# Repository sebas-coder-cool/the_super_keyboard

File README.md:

[keyboard (1).csv](https://github.com/user-attachments/files/33207110/keyboard.1.csv)
# The Super Keyboard

The Super Keyboard is an amazing keyboard that lets you attach a detachable screen. 
This screen can transform into a digital notebook — and the best part is that you
can also set up your Spotify on it.
## Features
- Clickable screen
- Digital notebook mode
- Detachable, dual-side screen mount

## Usage
Using the keyboard is simple: just connect it to your computer and start typing. 
Attach the screen to take notes directly on the digital notebook.

## License
- *cc by-nc-sa 4.0*
- full licence link: https://creativecommons.org/licenses/by-nc-sa/4.0/legalcode

## bom

[Bekijk de BOM](docs/BOM.csv)
## img

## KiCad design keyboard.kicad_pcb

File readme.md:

# the_keyboard

*A short description of the keyboard/project*

* Keyboard Maintainer: [sebastian](https://github.com/sebas-coder-cool)
* Hardware Supported: *The PCBs, controllers supported*
* Hardware Availability: *Links to where you can find this hardware*

Make example for this keyboard (after setting up your build environment):

    make the_keyboard:default

Flashing example for this keyboard:

    make the_keyboard:default:flash

See the [build environment setup](https://docs.qmk.fm/#/getting_started_build_tools) and the [make instructions](https://docs.qmk.fm/#/getting_started_make_guide) for more information. Brand new to QMK? Start with our [Complete Newbs Guide](https://docs.qmk.fm/#/newbs).

## Bootloader

Enter the bootloader in 3 ways:

* **Bootmagic reset**: Hold down the key at (0,0) in the matrix (usually the top left key or Escape) and plug in the keyboard
* **Physical reset button**: Briefly press the button on the back of the PCB - some may have pads you must short instead
* **Keycode in layout**: Press the key mapped to `QK_BOOT` if it is available

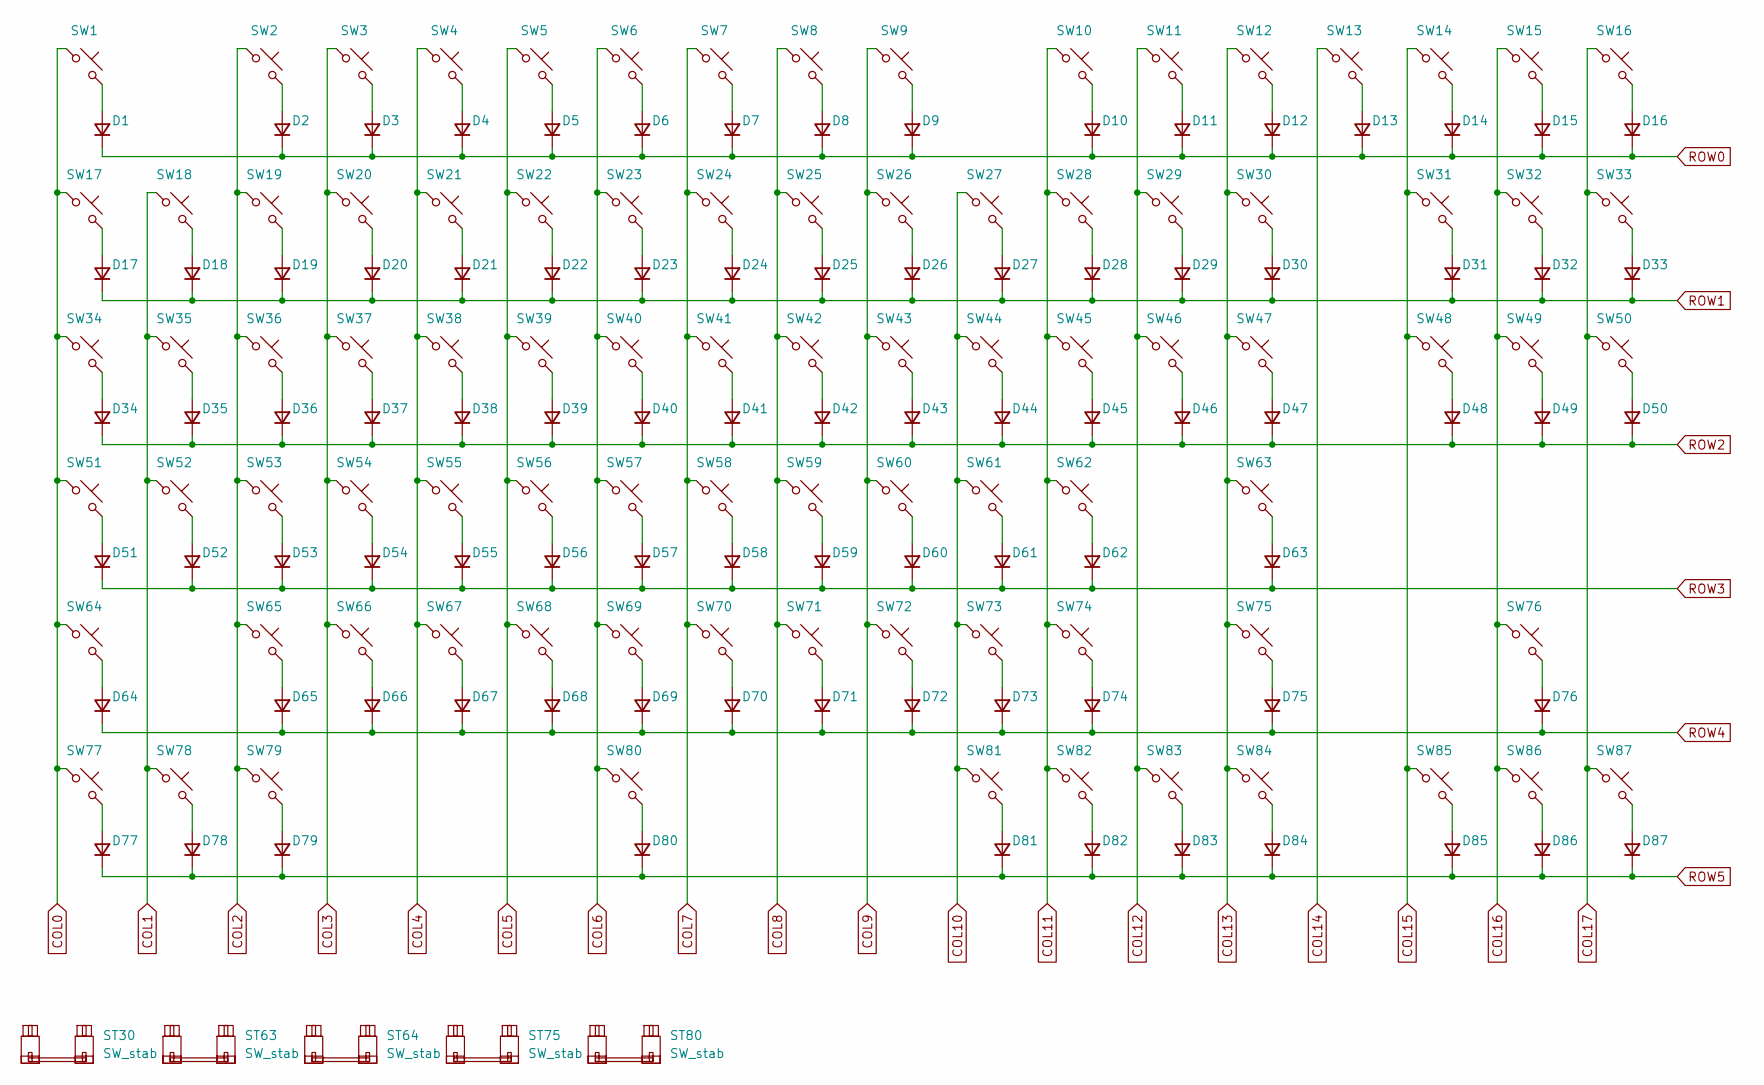
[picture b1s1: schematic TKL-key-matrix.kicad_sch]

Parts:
D1, D2, D3, D4, D5, D6, D7, D8, D9, D10, D11, D12, D13, D14, D15, D16, D17, D18, D19, D20, D21, D22, D23, D24, D25, D26, D27, D28, D29, D30, D31, D32, D33, D34, D35, D36, D37, D38, D39, D40, D41, D42, D43, D44, D45, D46, D47, D48, D49, D50, D51, D52, D53, D54, D55, D56, D57, D58, D59, D60, D61, D62, D63, D64, D65, D66, D67, D68, D69, D70, D71, D72, D73, D74, D75, D76, D77, D78, D79, D80, D81, D82, D83, D84, D85, D86, D87: D; D_SOD-123F
ST30, ST63, ST64, ST75: SW_stab; Stabilizer_Cherry_MX_2.00u
ST80: SW_stab; Stabilizer_Cherry_MX_6.25u
SW1, SW2, SW3, SW4, SW5, SW6, SW7, SW8, SW9, SW10, SW11, SW12, SW13, SW14, SW15, SW16, SW17, SW18, SW19, SW20, SW21, SW22, SW23, SW24, SW25, SW26, SW27, SW28, SW29, SW31, SW32, SW33, SW35, SW36, SW37, SW38, SW39, SW40, SW41, SW42, SW43, SW44, SW45, SW46, SW48, SW49, SW50, SW52, SW53, SW54, SW55, SW56, SW57, SW58, SW59, SW60, SW61, SW62, SW65, SW66, SW67, SW68, SW69, SW70, SW71, SW72, SW73, SW74, SW76, SW85, SW86, SW87: SW_Push; SW_Cherry_MX_PCB_1.00u
SW30: SW_Push; SW_Cherry_MX_PCB_2.00u
SW34, SW47: SW_Push; SW_Cherry_MX_PCB_1.50u
SW51: SW_Push; SW_Cherry_MX_PCB_1.75u
SW63, SW64: SW_Push; SW_Cherry_MX_PCB_2.25u
SW75: SW_Push; SW_Cherry_MX_PCB_2.75u
SW77, SW78, SW79, SW81, SW82, SW83, SW84: SW_Push; SW_Cherry_MX_PCB_1.25u
SW80: SW_Push; SW_Cherry_MX_PCB_6.25u

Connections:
COL0: SW1.1, SW17.1, SW34.1, SW51.1, SW64.1, SW77.1; also elsewhere on the board
COL1: SW18.1, SW35.1, SW52.1, SW78.1; also elsewhere on the board
COL2: SW2.1, SW19.1, SW36.1, SW53.1, SW65.1, SW79.1; also elsewhere on the board
COL3: SW3.1, SW20.1, SW37.1, SW54.1, SW66.1; also elsewhere on the board
COL4: SW4.1, SW21.1, SW38.1, SW55.1, SW67.1; also elsewhere on the board
COL5: SW5.1, SW22.1, SW39.1, SW56.1, SW68.1; also elsewhere on the board
COL6: SW6.1, SW23.1, SW40.1, SW57.1, SW69.1, SW80.1; also elsewhere on the board
COL7: SW7.1, SW24.1, SW41.1, SW58.1, SW70.1; also elsewhere on the board
COL8: SW8.1, SW25.1, SW42.1, SW59.1, SW71.1; also elsewhere on the board
COL9: SW9.1, SW26.1, SW43.1, SW60.1, SW72.1; also elsewhere on the board
COL10: SW27.1, SW44.1, SW61.1, SW73.1, SW81.1; also elsewhere on the board
COL11: SW10.1, SW28.1, SW45.1, SW62.1, SW74.1, SW82.1; also elsewhere on the board
COL12: SW11.1, SW29.1, SW46.1, SW83.1; also elsewhere on the board
COL13: SW12.1, SW30.1, SW47.1, SW63.1, SW75.1, SW84.1; also elsewhere on the board
COL14: SW13.1; also elsewhere on the board
COL15: SW14.1, SW31.1, SW48.1, SW85.1; also elsewhere on the board
COL16: SW15.1, SW32.1, SW49.1, SW76.1, SW86.1; also elsewhere on the board
COL17: SW16.1, SW33.1, SW50.1, SW87.1; also elsewhere on the board
unnamed: D1.2 (A), SW1.2
unnamed: D2.2 (A), SW2.2
unnamed: D3.2 (A), SW3.2
unnamed: D4.2 (A), SW4.2
unnamed: D5.2 (A), SW5.2
unnamed: D6.2 (A), SW6.2
unnamed: D7.2 (A), SW7.2
unnamed: D8.2 (A), SW8.2
unnamed: D9.2 (A), SW9.2
unnamed: D10.2 (A), SW10.2
unnamed: D11.2 (A), SW11.2
unnamed: D12.2 (A), SW12.2
unnamed: D13.2 (A), SW13.2
unnamed: D14.2 (A), SW14.2
unnamed: D15.2 (A), SW15.2
unnamed: D16.2 (A), SW16.2
unnamed: D17.2 (A), SW17.2
unnamed: D18.2 (A), SW18.2
unnamed: D19.2 (A), SW19.2
unnamed: D20.2 (A), SW20.2
unnamed: D21.2 (A), SW21.2
unnamed: D22.2 (A), SW22.2
unnamed: D23.2 (A), SW23.2
unnamed: D24.2 (A), SW24.2
unnamed: D25.2 (A), SW25.2
unnamed: D26.2 (A), SW26.2
unnamed: D27.2 (A), SW27.2
unnamed: D28.2 (A), SW28.2
unnamed: D29.2 (A), SW29.2
unnamed: D30.2 (A), SW30.2
unnamed: D31.2 (A), SW31.2
unnamed: D32.2 (A), SW32.2
unnamed: D33.2 (A), SW33.2
unnamed: D34.2 (A), SW34.2
unnamed: D35.2 (A), SW35.2
unnamed: D36.2 (A), SW36.2
unnamed: D37.2 (A), SW37.2
unnamed: D38.2 (A), SW38.2
unnamed: D39.2 (A), SW39.2
unnamed: D40.2 (A), SW40.2
unnamed: D41.2 (A), SW41.2
unnamed: D42.2 (A), SW42.2
unnamed: D43.2 (A), SW43.2
unnamed: D44.2 (A), SW44.2
unnamed: D45.2 (A), SW45.2
unnamed: D46.2 (A), SW46.2
unnamed: D47.2 (A), SW47.2
unnamed: D48.2 (A), SW48.2
unnamed: D49.2 (A), SW49.2
unnamed: D50.2 (A), SW50.2
unnamed: D51.2 (A), SW51.2
unnamed: D52.2 (A), SW52.2
unnamed: D53.2 (A), SW53.2
unnamed: D54.2 (A), SW54.2
unnamed: D55.2 (A), SW55.2
unnamed: D56.2 (A), SW56.2
unnamed: D57.2 (A), SW57.2
unnamed: D58.2 (A), SW58.2
unnamed: D59.2 (A), SW59.2
unnamed: D60.2 (A), SW60.2
unnamed: D61.2 (A), SW61.2
unnamed: D62.2 (A), SW62.2
unnamed: D63.2 (A), SW63.2
unnamed: D64.2 (A), SW64.2
unnamed: D65.2 (A), SW65.2
unnamed: D66.2 (A), SW66.2
unnamed: D67.2 (A), SW67.2
unnamed: D68.2 (A), SW68.2
unnamed: D69.2 (A), SW69.2
unnamed: D70.2 (A), SW70.2
unnamed: D71.2 (A), SW71.2
unnamed: D72.2 (A), SW72.2
unnamed: D73.2 (A), SW73.2
unnamed: D74.2 (A), SW74.2
unnamed: D75.2 (A), SW75.2
unnamed: D76.2 (A), SW76.2
unnamed: D77.2 (A), SW77.2
unnamed: D78.2 (A), SW78.2
unnamed: D79.2 (A), SW79.2
unnamed: D80.2 (A), SW80.2
unnamed: D81.2 (A), SW81.2
unnamed: D82.2 (A), SW82.2
unnamed: D83.2 (A), SW83.2
unnamed: D84.2 (A), SW84.2
unnamed: D85.2 (A), SW85.2
unnamed: D86.2 (A), SW86.2
unnamed: D87.2 (A), SW87.2
ROW0: D1.1 (K), D2.1 (K), D3.1 (K), D4.1 (K), D5.1 (K), D6.1 (K), D7.1 (K), D8.1 (K), D9.1 (K), D10.1 (K), D11.1 (K), D12.1 (K), D13.1 (K), D14.1 (K), D15.1 (K), D16.1 (K); also elsewhere on the board
ROW1: D17.1 (K), D18.1 (K), D19.1 (K), D20.1 (K), D21.1 (K), D22.1 (K), D23.1 (K), D24.1 (K), D25.1 (K), D26.1 (K), D27.1 (K), D28.1 (K), D29.1 (K), D30.1 (K), D31.1 (K), D32.1 (K), D33.1 (K); also elsewhere on the board
ROW2: D34.1 (K), D35.1 (K), D36.1 (K), D37.1 (K), D38.1 (K), D39.1 (K), D40.1 (K), D41.1 (K), D42.1 (K), D43.1 (K), D44.1 (K), D45.1 (K), D46.1 (K), D47.1 (K), D48.1 (K), D49.1 (K), D50.1 (K); also elsewhere on the board
ROW3: D51.1 (K), D52.1 (K), D53.1 (K), D54.1 (K), D55.1 (K), D56.1 (K), D57.1 (K), D58.1 (K), D59.1 (K), D60.1 (K), D61.1 (K), D62.1 (K), D63.1 (K); also elsewhere on the board
ROW4: D64.1 (K), D65.1 (K), D66.1 (K), D67.1 (K), D68.1 (K), D69.1 (K), D70.1 (K), D71.1 (K), D72.1 (K), D73.1 (K), D74.1 (K), D75.1 (K), D76.1 (K); also elsewhere on the board
ROW5: D77.1 (K), D78.1 (K), D79.1 (K), D80.1 (K), D81.1 (K), D82.1 (K), D83.1 (K), D84.1 (K), D85.1 (K), D86.1 (K), D87.1 (K); also elsewhere on the board

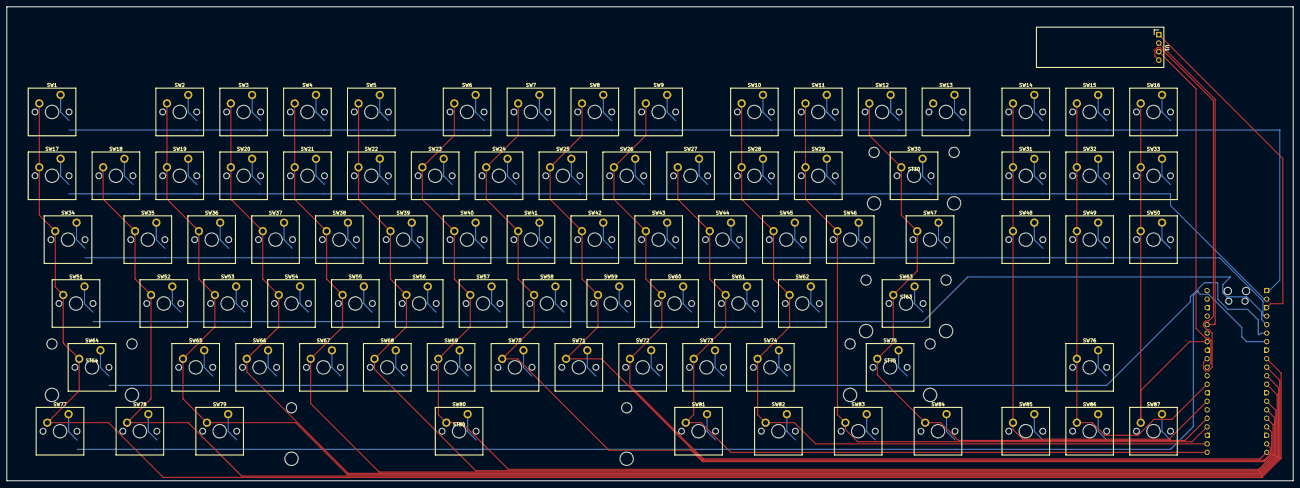
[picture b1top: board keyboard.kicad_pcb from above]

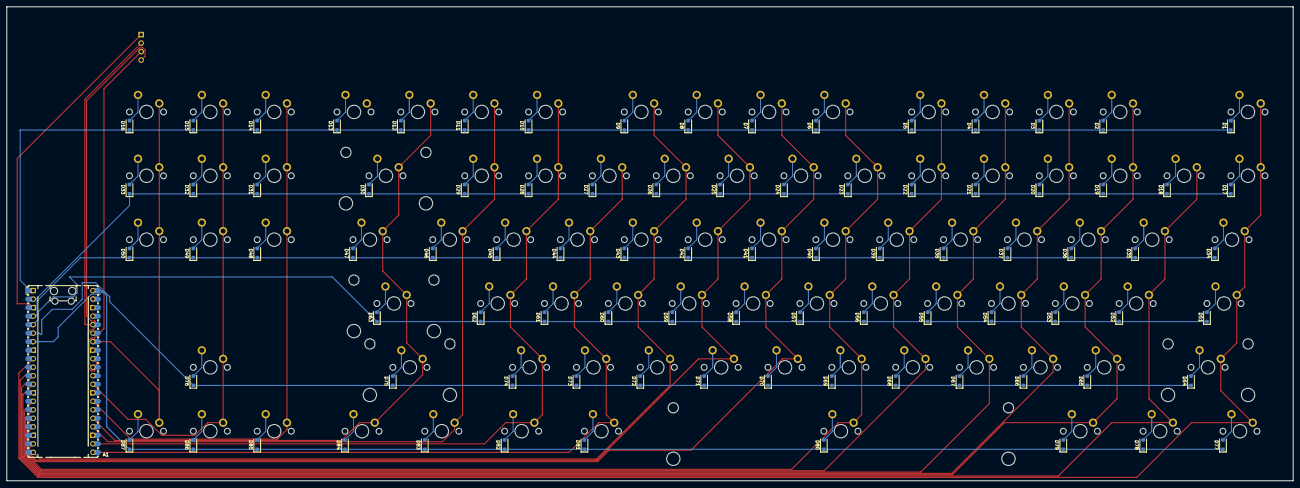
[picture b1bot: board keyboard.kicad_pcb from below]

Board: 2 copper layers, 383.8 x 141.4 mm, 181 parts (88 on the bottom side), 115 nets.

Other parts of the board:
A1: RaspberryPi_Pico; RaspberryPi_Pico_Common_Unspecified
U1: ER_OLEDM0.91_1x-I2C

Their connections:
COL0: A1.9 (GPIO6); also elsewhere on the board
COL1: A1.10 (GPIO7); also elsewhere on the board
COL2: A1.11 (GPIO8); also elsewhere on the board
COL3: A1.12 (GPIO9); also elsewhere on the board
COL4: A1.14 (GPIO10); also elsewhere on the board
COL5: A1.15 (GPIO11); also elsewhere on the board
COL6: A1.16 (GPIO12); also elsewhere on the board
COL7: A1.17 (GPIO13); also elsewhere on the board
COL8: A1.19 (GPIO14); also elsewhere on the board
COL9: A1.20 (GPIO15); also elsewhere on the board
COL10: A1.21 (GPIO16); also elsewhere on the board
COL11: A1.22 (GPIO17); also elsewhere on the board
COL12: A1.24 (GPIO18); also elsewhere on the board
COL13: A1.25 (GPIO19); also elsewhere on the board
COL14: A1.26 (GPIO20); also elsewhere on the board
COL15: A1.27 (GPIO21); also elsewhere on the board
COL16: A1.29 (GPIO22); also elsewhere on the board
COL17: A1.34 (GPIO28_ADC2); also elsewhere on the board
unnamed: A1.36 (3V3), U1.2 (VCC)
unnamed: A1.31 (GPIO26_ADC0), U1.3 (SCL)
unnamed: A1.32 (GPIO27_ADC1), U1.4 (SDA)
unnamed: A1.3 (GND), A1.8 (GND), A1.13 (GND), A1.18 (GND), A1.23 (GND), A1.28 (GND), A1.38 (GND), U1.1 (GND)
ROW0: A1.1 (GPIO0); also elsewhere on the board
ROW1: A1.2 (GPIO1); also elsewhere on the board
ROW2: A1.4 (GPIO2); also elsewhere on the board
ROW3: A1.5 (GPIO3); also elsewhere on the board
ROW4: A1.6 (GPIO4); also elsewhere on the board
ROW5: A1.7 (GPIO5); also elsewhere on the board
